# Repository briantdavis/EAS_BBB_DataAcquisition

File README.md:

# EagleAeroSport BeagleBone Black
# Data Acquisition System

This REPO is intended to be extracted into the folder /EAS on the beaglebone black.

Contains code C++ compiled directly on the BBB, using the debian GCC tool chain.

Key files:<br>
PCA9544 - I2C Mux<br>
ADXL345 - I2C 3-axis Accelerometer<br>
BME280  - I2C Pressure, Humidity & Temperature<br>
MPU6050 - I2C 3-axis Accelerometer & 3-axis Gyro<br>
hscPress- AMSYS AMS59xx series pressure sensors<br>

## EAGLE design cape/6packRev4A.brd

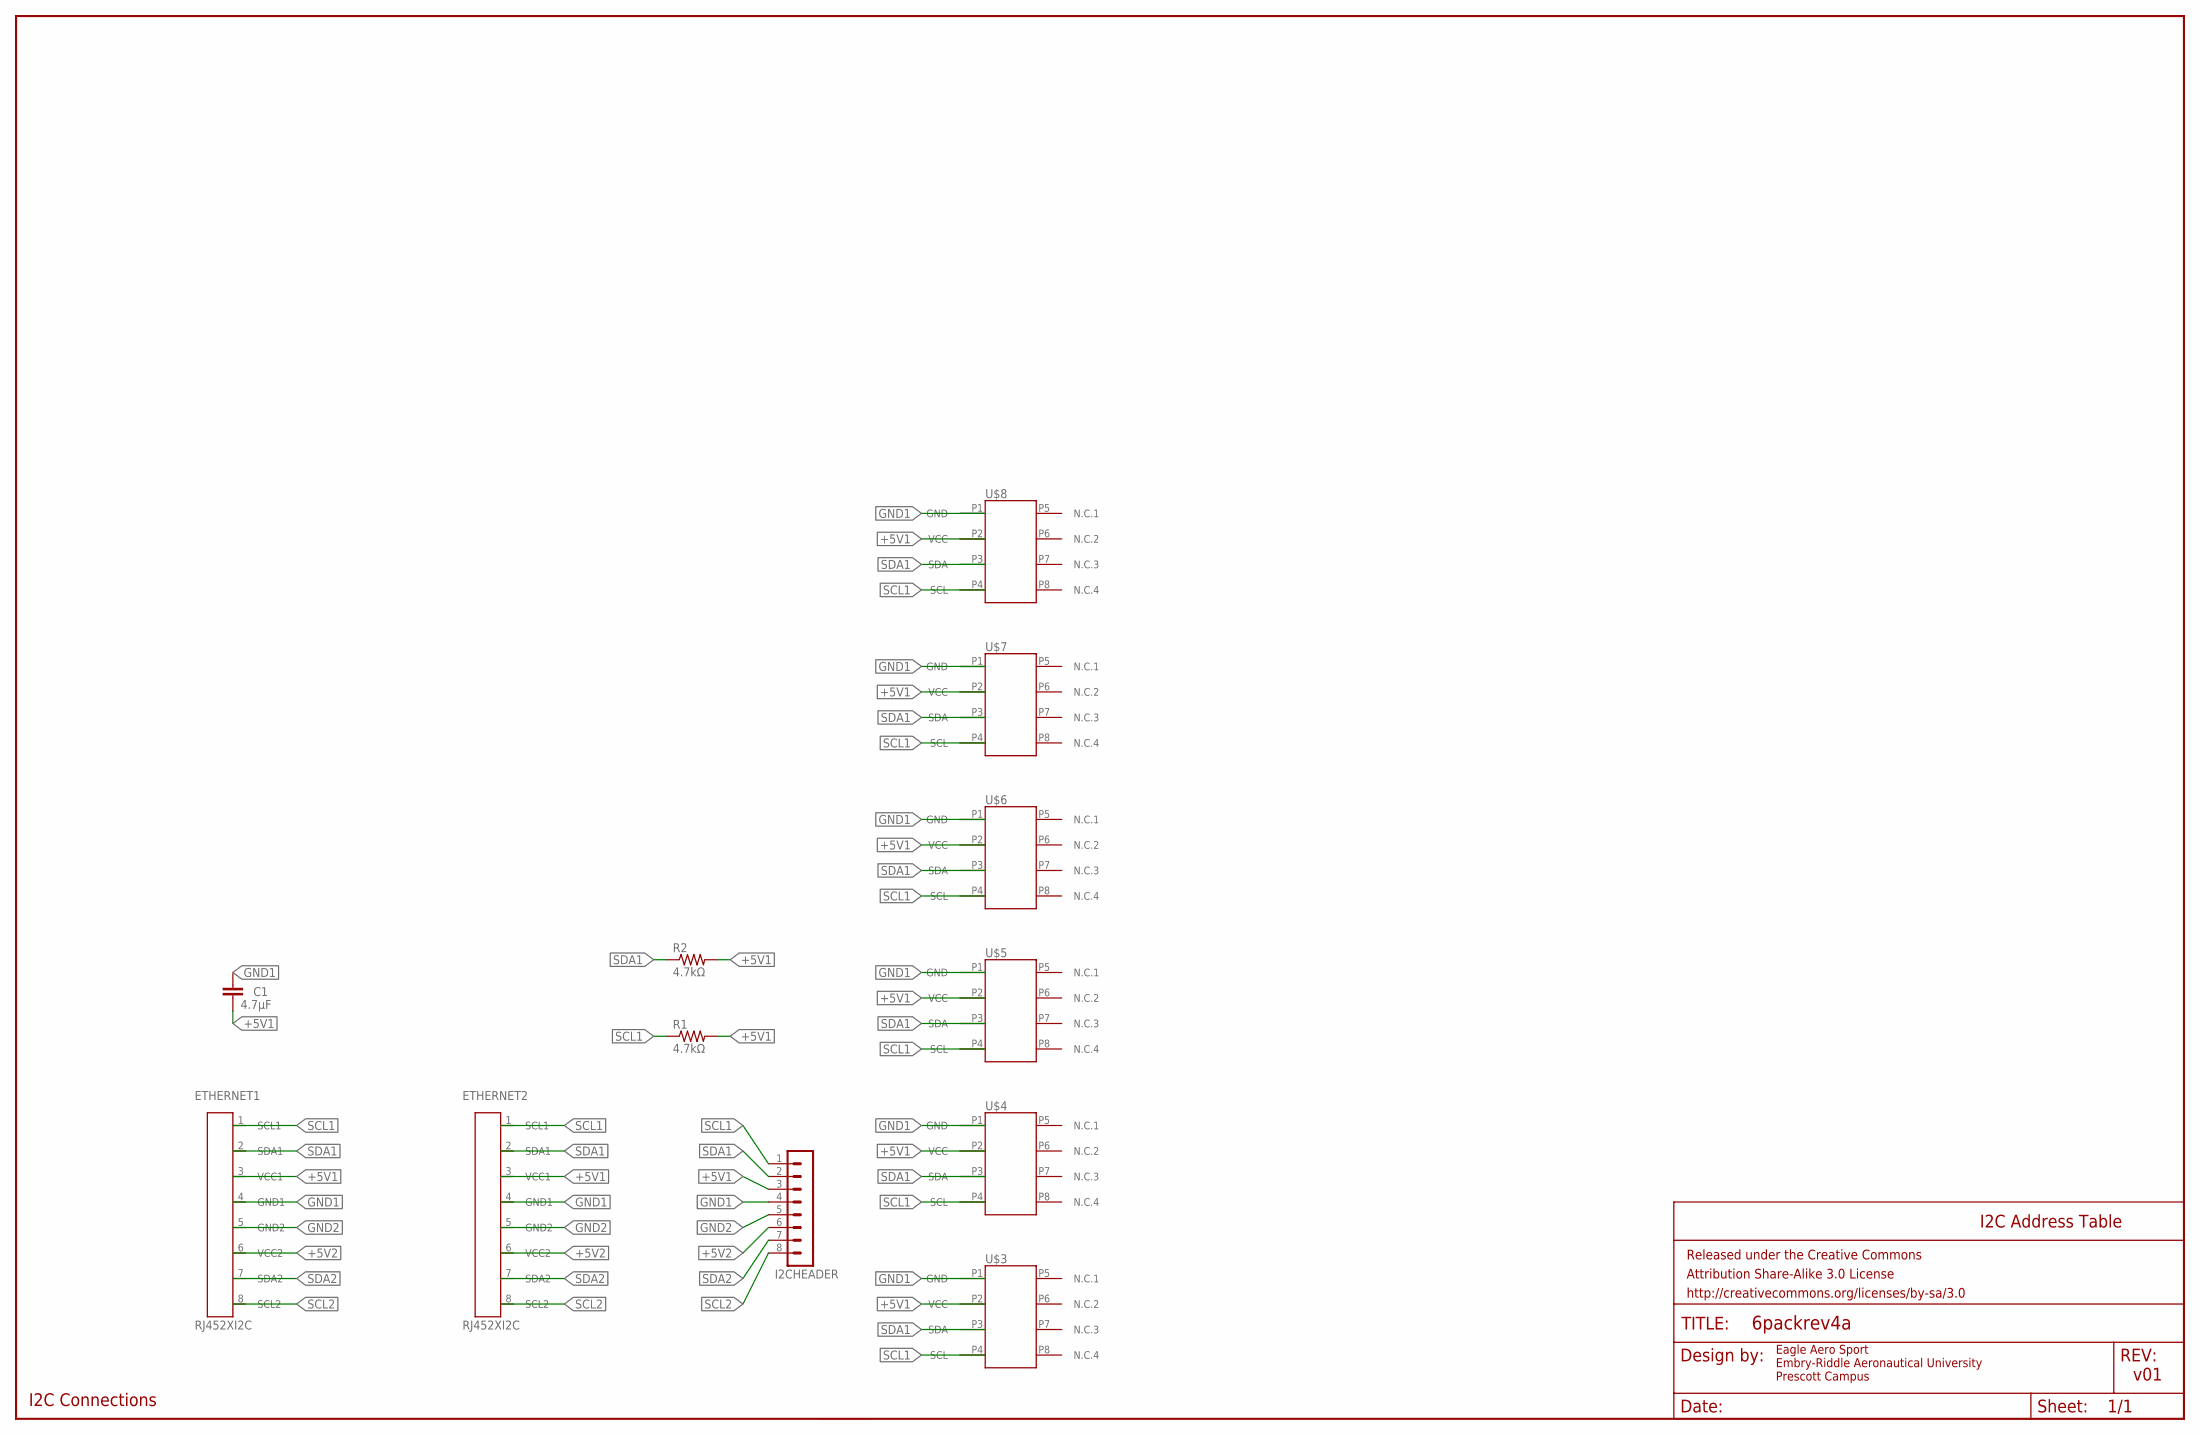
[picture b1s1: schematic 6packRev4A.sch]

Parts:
C1: 4.7µF; CAP-PTH-10MM
ETHERNET1, ETHERNET2: RJ452XI2C; RJ45-8
FRAME1: FRAME-LEDGER; CREATIVE_COMMONS
I2CHEADER: MA08-1
R1, R2: 4.7kΩ; 0207/12
U$3, U$4, U$5, U$6, U$7, U$8: AMS5915; DIP8W

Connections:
+5V1: C1.2, ETHERNET1.3 (VCC1), ETHERNET2.3 (VCC1), I2CHEADER.3, R1.2, R2.2, U$3.P2 (VCC), U$4.P2 (VCC), U$5.P2 (VCC), U$6.P2 (VCC), U$7.P2 (VCC), U$8.P2 (VCC)
+5V2: ETHERNET1.6 (VCC2), ETHERNET2.6 (VCC2), I2CHEADER.6
GND1: C1.1, ETHERNET1.4 (GND1), ETHERNET2.4 (GND1), I2CHEADER.4, U$3.P1 (GND), U$4.P1 (GND), U$5.P1 (GND), U$6.P1 (GND), U$7.P1 (GND), U$8.P1 (GND)
GND2: ETHERNET1.5 (GND2), ETHERNET2.5 (GND2), I2CHEADER.5
SCL1: ETHERNET1.1 (SCL1), ETHERNET2.1 (SCL1), I2CHEADER.1, R1.1, U$3.P4 (SCL), U$4.P4 (SCL), U$5.P4 (SCL), U$6.P4 (SCL), U$7.P4 (SCL), U$8.P4 (SCL)
SCL2: ETHERNET1.8 (SCL2), ETHERNET2.8 (SCL2), I2CHEADER.8
SDA1: ETHERNET1.2 (SDA1), ETHERNET2.2 (SDA1), I2CHEADER.2, R2.1, U$3.P3 (SDA), U$4.P3 (SDA), U$5.P3 (SDA), U$6.P3 (SDA), U$7.P3 (SDA), U$8.P3 (SDA)
SDA2: ETHERNET1.7 (SDA2), ETHERNET2.7 (SDA2), I2CHEADER.7

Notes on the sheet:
I2C Address Table
v01
Eagle Aero Sport Embry-Riddle Aeronautical University Prescott Campus
I2C Connections

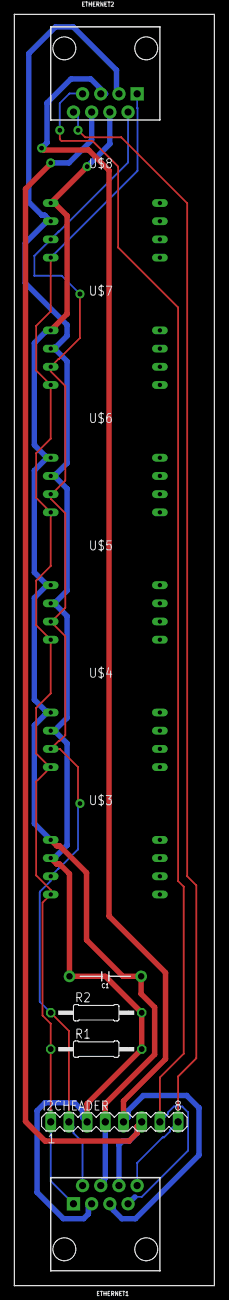
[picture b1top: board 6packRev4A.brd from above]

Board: 2 copper layers, 27.9 x 177.5 mm, 13 parts (0 on the bottom side), 8 nets.

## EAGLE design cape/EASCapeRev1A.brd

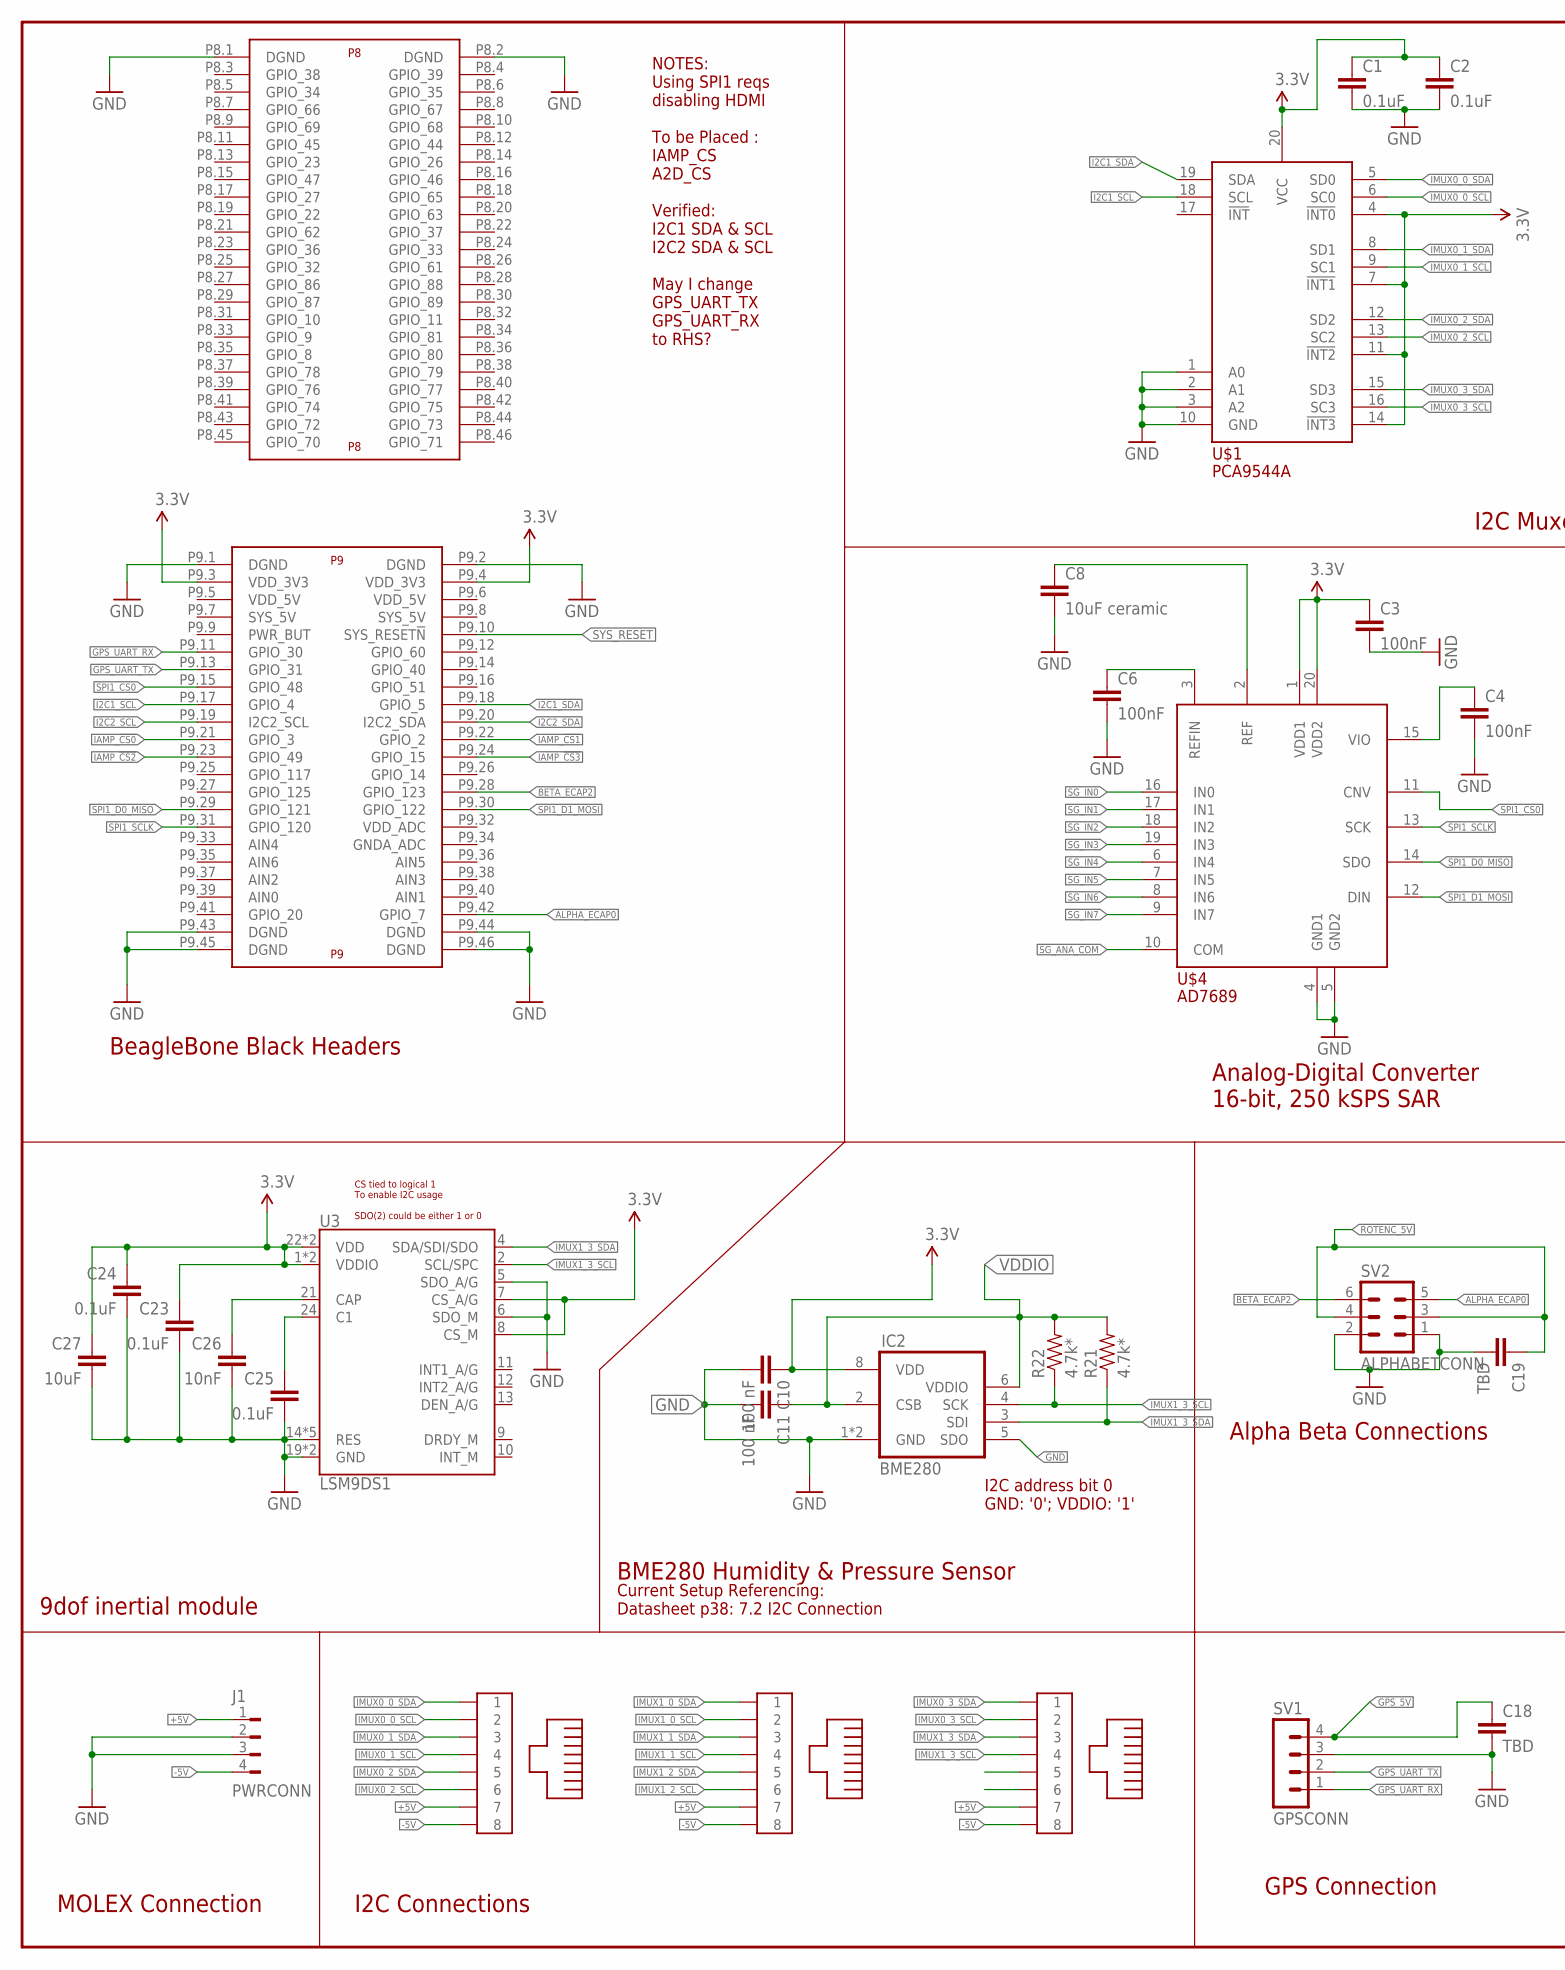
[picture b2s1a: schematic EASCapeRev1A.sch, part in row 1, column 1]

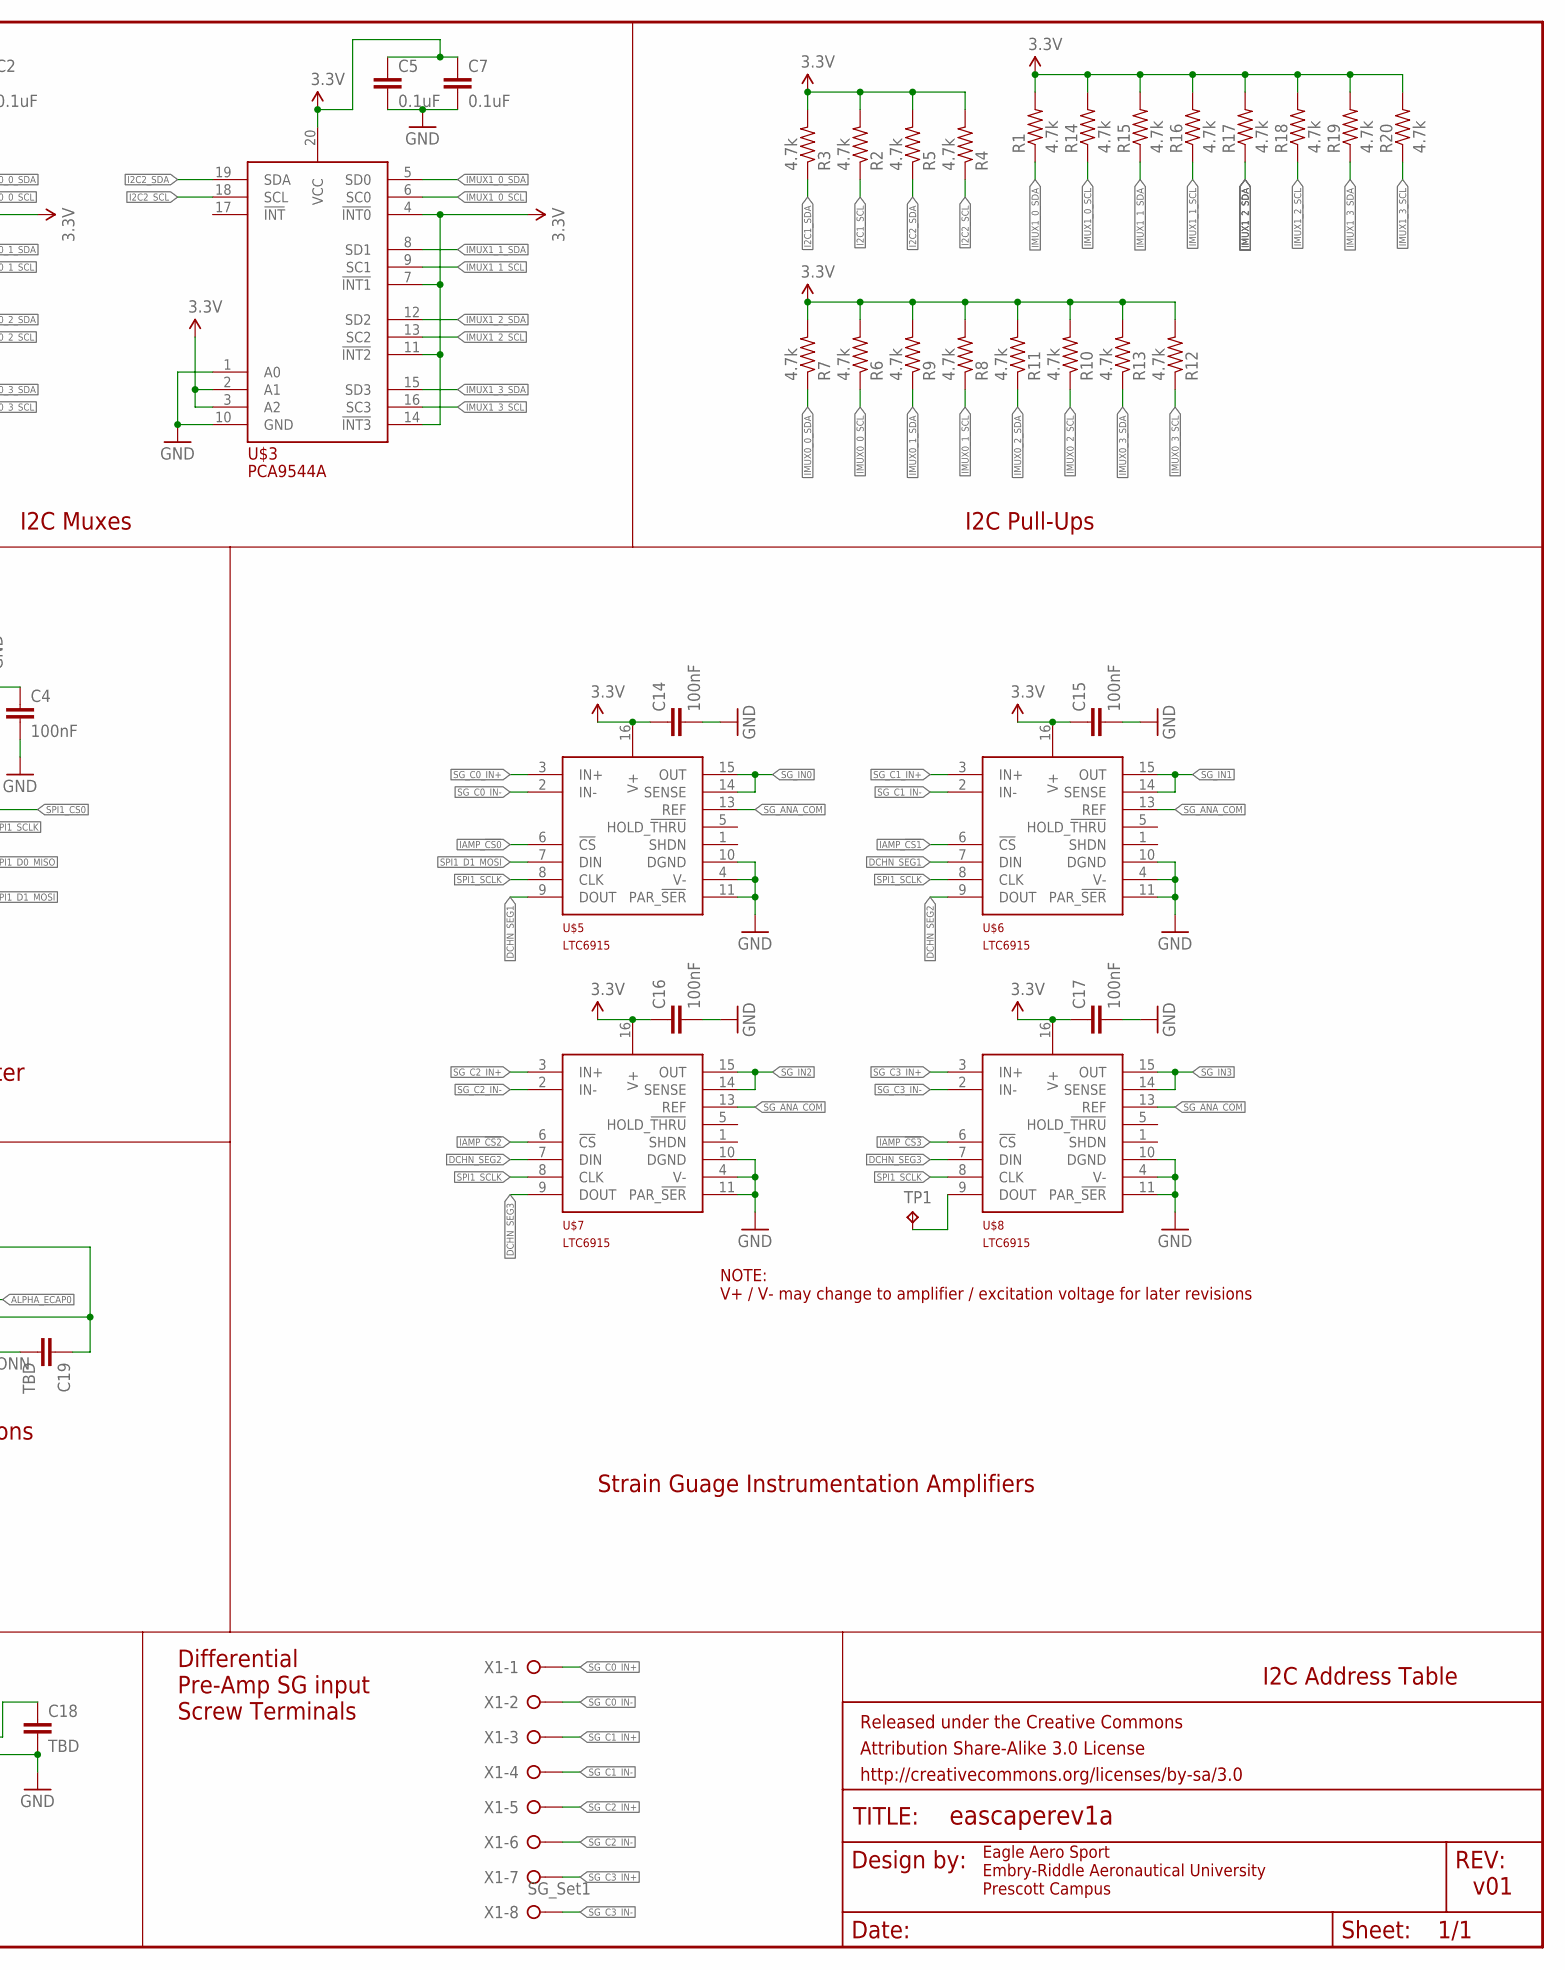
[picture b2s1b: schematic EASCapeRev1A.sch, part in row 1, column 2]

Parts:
C1, C2, C5, C7, C23, C24, C25: 0.1uF; 0805
C3, C4, C6, C14, C15, C16, C17: 100nF; 0805
C8: 10uF ceramic; 0805
C10, C11: 100 nF; 0805
C18, C19: TBD; 0805
C26: 10nF; 0805
C27: 10uF; 0805
FRAME1: FRAME-LEDGER; CREATIVE_COMMONS
IC2: BME280
J1: PWRCONN; 350211
R1, R2, R3, R4, R5, R6, R7, R8, R9, R10, R11, R12, R13, R14, R15, R16, R17, R18, R19, R20: 4.7k; 0805
R21, R22: 4.7k*; 0805
RJ1, RJ2, RJ3: MOLEX-RJ45-SMT
SV1: GPSCONN; MA04-1
SV2: ALPHABETCONN; MA03-2
TP1: TPTP08R; TP08R
U3: LSM9DS1; LGA24-8X4
U$1, U$3: PCA9544A; TSSOP20
U$2: BEAGLE_BONE_BLACK_CAPE
U$4: AD7689; QFN20
U$5, U$6, U$7, U$8: LTC6915; SSOP16
X1: SG_Set1; W237-8P

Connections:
3.3V: C1.1, C2.1, C3.1, C5.1, C7.1, C10.1, C14.1, C15.1, C16.1, C17.1, C23.1, C24.1, C27.1, IC2.8 (VDD), R1.2, R2.2, R3.2, R4.2, R5.2, R6.2, R7.2, R8.2, R9.2, R10.2, R11.2, R12.2, R13.2, R14.2, R15.2, R16.2, R17.2, R18.2, R19.2, R20.2, U3.1 (VDDIO), U3.3 (VDDIO), U3.7 (CS_A/G), U3.8 (CS_M), U3.22 (VDD), U3.23 (VDD), U$1.4 (!INT0!), U$1.7 (!INT1!), U$1.11 (!INT2!), U$1.14 (!INT3!), U$1.20 (VCC), U$2.P9.3 (VDD_3V3), U$2.P9.4 (VDD_3V3), U$3.2 (A1), U$3.3 (A2), U$3.4 (!INT0!), U$3.7 (!INT1!), U$3.11 (!INT2!), U$3.14 (!INT3!), U$3.20 (VCC), U$4.1 (VDD1), U$4.20 (VDD2), U$5.16 (V+), U$6.16 (V+), U$7.16 (V+), U$8.16 (V+)
+5V: J1.1, RJ1.7, RJ2.7, RJ3.7
-5V: J1.4, RJ1.8, RJ2.8, RJ3.8
ALPHA_ECAP0: SV2.5, U$2.P9.42 (GPIO_7)
BETA_ECAP2: SV2.6, U$2.P9.28 (GPIO_123)
C1: C25.1, U3.24 (C1)
CAP: C26.1, U3.21 (CAP)
DCHN_SEG1: U$5.9 (DOUT), U$6.7 (DIN)
DCHN_SEG2: U$6.9 (DOUT), U$7.7 (DIN)
DCHN_SEG3: U$7.9 (DOUT), U$8.7 (DIN)
GND: C1.2, C2.2, C3.2, C4.2, C5.2, C6.2, C7.2, C8.2, C10.2, C11.2, C14.2, C15.2, C16.2, C17.2, C18.2, C19.2, C23.2, C24.2, C25.2, C26.2, C27.2, IC2.1 (GND), IC2.5 (SDO), IC2.7 (GND), J1.2, J1.3, SV1.3, SV2.1, SV2.2, U3.5 (SDO_A/G), U3.6 (SDO_M), U3.14 (RES), U3.15 (RES), U3.16 (RES), U3.17 (RES), U3.18 (RES), U3.19 (GND), U3.20 (GND), U$1.1 (A0), U$1.2 (A1), U$1.3 (A2), U$1.10 (GND), U$2.P8.1 (DGND), U$2.P8.2 (DGND), U$2.P9.1 (DGND), U$2.P9.2 (DGND), U$2.P9.43 (DGND), U$2.P9.44 (DGND), U$2.P9.45 (DGND), U$2.P9.46 (DGND), U$3.1 (A0), U$3.10 (GND), U$4.4 (GND1), U$4.5 (GND2), U$5.4 (V-), U$5.10 (DGND), U$5.11 (PAR_!SER!), U$6.4 (V-), U$6.10 (DGND), U$6.11 (PAR_!SER!), U$7.4 (V-), U$7.10 (DGND), U$7.11 (PAR_!SER!), U$8.4 (V-), U$8.10 (DGND), U$8.11 (PAR_!SER!)
GPS_5V: C18.1, SV1.4
GPS_UART_RX: SV1.1, U$2.P9.11 (GPIO_30)
GPS_UART_TX: SV1.2, U$2.P9.13 (GPIO_31)
I2C1_SCL: R2.1, U$1.18 (SCL), U$2.P9.17 (GPIO_4)
I2C1_SDA: R3.1, U$1.19 (SDA), U$2.P9.18 (GPIO_5)
I2C2_SCL: R4.1, U$2.P9.19 (I2C2_SCL), U$3.18 (SCL)
I2C2_SDA: R5.1, U$2.P9.20 (I2C2_SDA), U$3.19 (SDA)
IAMP_!CS0!: U$2.P9.21 (GPIO_3), U$5.6 (!CS!)
IAMP_!CS1!: U$2.P9.22 (GPIO_2), U$6.6 (!CS!)
IAMP_!CS2!: U$2.P9.23 (GPIO_49), U$7.6 (!CS!)
IAMP_!CS3!: U$2.P9.24 (GPIO_15), U$8.6 (!CS!)
IMUX0_0_SCL: R6.1, RJ1.2, U$1.6 (SC0)
IMUX0_0_SDA: R7.1, RJ1.1, U$1.5 (SD0)
IMUX0_1_SCL: R8.1, RJ1.4, U$1.9 (SC1)
IMUX0_1_SDA: R9.1, RJ1.3, U$1.8 (SD1)
IMUX0_2_SCL: R10.1, RJ1.6, U$1.13 (SC2)
IMUX0_2_SDA: R11.1, RJ1.5, U$1.12 (SD2)
IMUX0_3_SCL: R12.1, RJ3.2, U$1.16 (SC3)
IMUX0_3_SDA: R13.1, RJ3.1, U$1.15 (SD3)
IMUX1_0_SCL: R14.1, RJ2.2, U$3.6 (SC0)
IMUX1_0_SDA: R1.1, RJ2.1, U$3.5 (SD0)
IMUX1_1_SCL: R16.1, RJ2.4, U$3.9 (SC1)
IMUX1_1_SDA: R15.1, RJ2.3, U$3.8 (SD1)
IMUX1_2_SCL: R18.1, RJ2.6, U$3.13 (SC2)
IMUX1_2_SDA: R17.1, RJ2.5, U$3.12 (SD2)
IMUX1_3_SCL: IC2.4 (SCK), R20.1, R22.1, RJ3.4, U3.2 (SCL/SPC), U$3.16 (SC3)
IMUX1_3_SDA: IC2.3 (SDI), R19.1, R21.1, RJ3.3, U3.4 (SDA/SDI/SDO), U$3.15 (SD3)
unnamed: C6.1, U$4.3 (REFIN)
unnamed: C8.1, U$4.2 (REF)
unnamed: C4.1, U$4.15 (VIO)
unnamed: TP1.TP, U$8.9 (DOUT)
ROTENC_5V: C19.1, SV2.3, SV2.4
SG_ANA_COM: U$4.10 (COM), U$5.13 (REF), U$6.13 (REF), U$7.13 (REF), U$8.13 (REF)
SG_C0_IN+: U$5.3 (IN+), X1.1
SG_C0_IN-: U$5.2 (IN-), X1.2
SG_C1_IN+: U$6.3 (IN+), X1.3
SG_C1_IN-: U$6.2 (IN-), X1.4
SG_C2_IN+: U$7.3 (IN+), X1.5
SG_C2_IN-: U$7.2 (IN-), X1.6
SG_C3_IN+: U$8.3 (IN+), X1.7
SG_C3_IN-: U$8.2 (IN-), X1.8
SG_IN0: U$4.16 (IN0), U$5.14 (SENSE), U$5.15 (OUT)
SG_IN1: U$4.17 (IN1), U$6.14 (SENSE), U$6.15 (OUT)
SG_IN2: U$4.18 (IN2), U$7.14 (SENSE), U$7.15 (OUT)
SG_IN3: U$4.19 (IN3), U$8.14 (SENSE), U$8.15 (OUT)
SG_IN4: U$4.6 (IN4)
SG_IN5: U$4.7 (IN5)
SG_IN6: U$4.8 (IN6)
SG_IN7: U$4.9 (IN7)
SPI1_CS0: U$2.P9.15 (GPIO_48), U$4.11 (CNV)
SPI1_D0_MISO: U$2.P9.29 (GPIO_121), U$4.14 (SDO)
SPI1_D1_MOSI: U$2.P9.30 (GPIO_122), U$4.12 (DIN), U$5.7 (DIN)
SPI1_SCLK: U$2.P9.31 (GPIO_120), U$4.13 (SCK), U$5.8 (CLK), U$6.8 (CLK), U$7.8 (CLK), U$8.8 (CLK)
SYS_RESET: U$2.P9.10 (SYS_RESET!N)
VDDIO: C11.1, IC2.2 (CSB), IC2.6 (VDDIO), R21.2, R22.2

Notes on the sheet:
BeagleBone Black Headers
I2C Address Table
v01
Eagle Aero Sport Embry-Riddle Aeronautical University Prescott Campus
I2C Muxes
Analog-Digital Converter 16-bit, 250 kSPS SAR
CS tied to logical 1 To enable I2C usage SDO(2) could be either 1 or 0
9dof inertial module
Strain Guage Instrumentation Amplifiers
Differential Pre-Amp SG input Screw Terminals
I2C Pull-Ups
I2C Connections
NOTES: Using SPI1 reqs disabling HDMI To be Placed : IAMP_CS A2D_CS Verified: I2C1 SDA & SCL I2C2 SDA & SCL May I change GPS_UART_TX GPS_UART_RX to RHS?
NOTE: V+ / V- may change to amplifier / excitation voltage for later revisions
GPS Connection
Alpha Beta Connections
MOLEX Connection
BME280 Humidity & Pressure Sensor
Current Setup Referencing: Datasheet p38: 7.2 I2C Connection
I2C address bit 0 GND: '0'; VDDIO: '1'

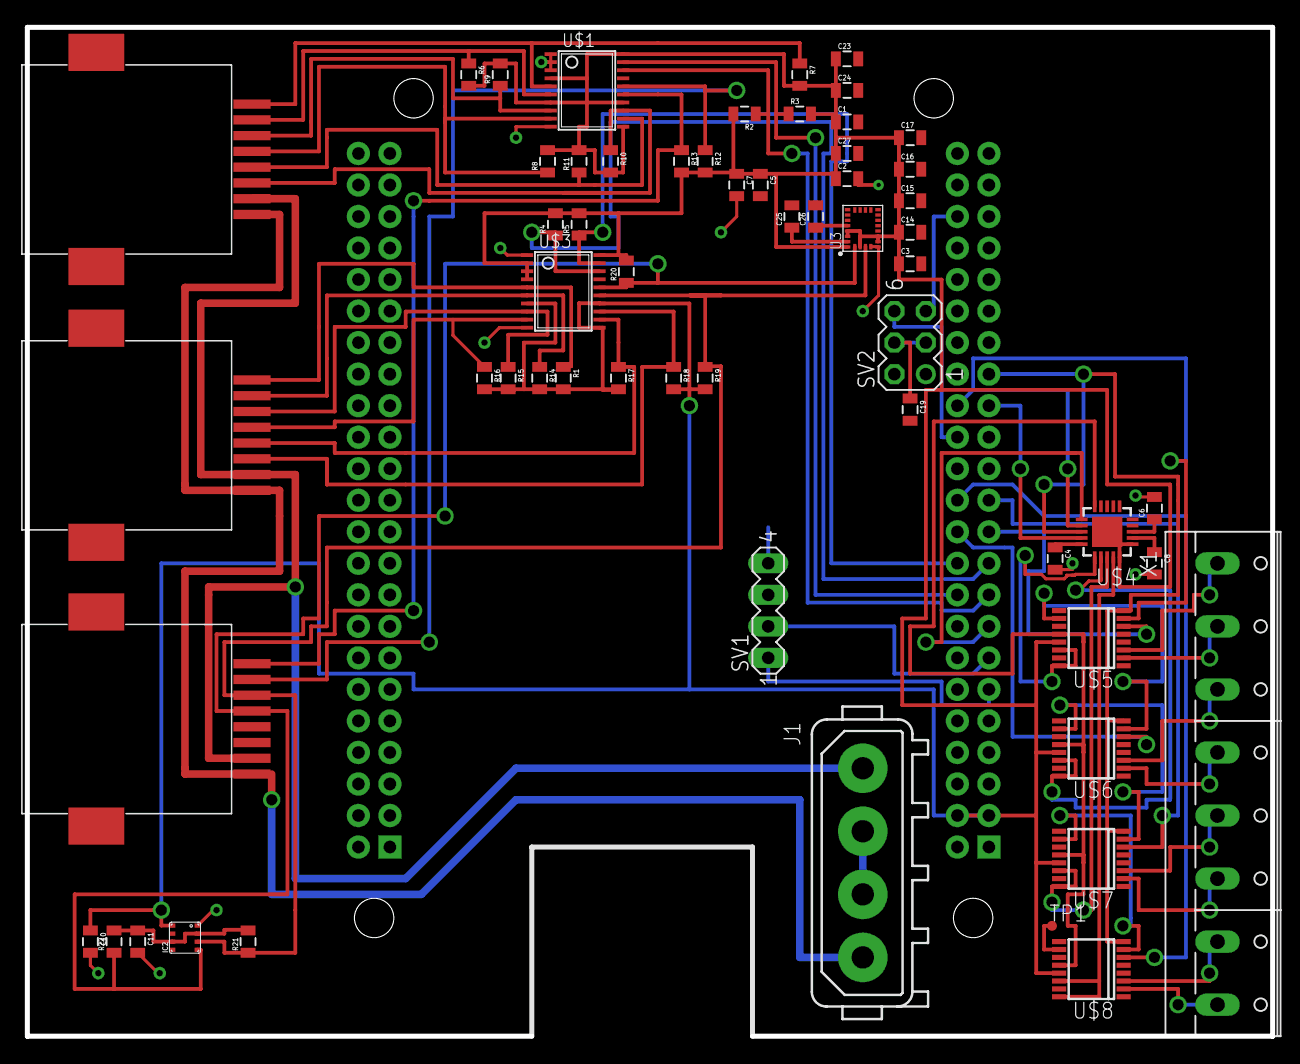
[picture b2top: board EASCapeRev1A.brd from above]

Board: 2 copper layers, 100.3 x 81.3 mm, 62 parts (1 on the bottom side), 61 nets.

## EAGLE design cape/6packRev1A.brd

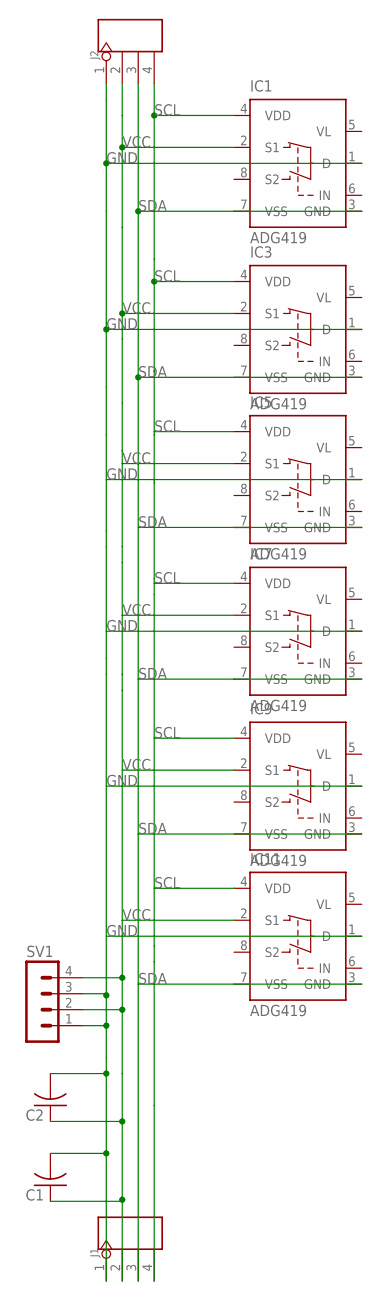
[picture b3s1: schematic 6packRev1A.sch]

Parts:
C1, C2: C-USC0805; C0805
IC1, IC3, IC5, IC7, IC9, IC11: ADG419; DIL08
J1, J2: HEADER-4P-80/40MIL; 4P-2.54-80/40MIL
SV1: MA04-1

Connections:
GND: C1.2, C2.2, IC1.1 (D), IC3.1 (D), IC5.1 (D), IC7.1 (D), IC9.1 (D), IC11.1 (D), J1.1, J2.1, SV1.1, SV1.3
SCL: IC1.4 (VDD), IC3.4 (VDD), IC5.4 (VDD), IC7.4 (VDD), IC9.4 (VDD), IC11.4 (VDD), J1.4, J2.4
SDA: IC1.3 (GND), IC1.7 (VSS), IC3.3 (GND), IC3.7 (VSS), IC5.3 (GND), IC5.7 (VSS), IC7.3 (GND), IC7.7 (VSS), IC9.3 (GND), IC11.3 (GND), J1.3, J2.3
VCC: C1.1, C2.1, IC1.2 (S1), IC3.2 (S1), IC5.2 (S1), IC7.2 (S1), IC9.2 (S1), IC11.2 (S1), J1.2, J2.2, SV1.2, SV1.4
VL: IC1.5 (VL), IC3.5 (VL), IC5.5 (VL), IC7.5 (VL), IC9.5 (VL), IC11.5 (VL)
VSS: IC9.7 (VSS), IC11.7 (VSS)

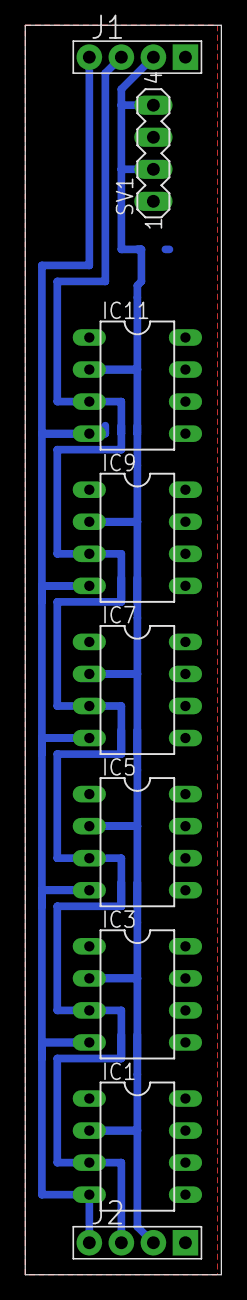
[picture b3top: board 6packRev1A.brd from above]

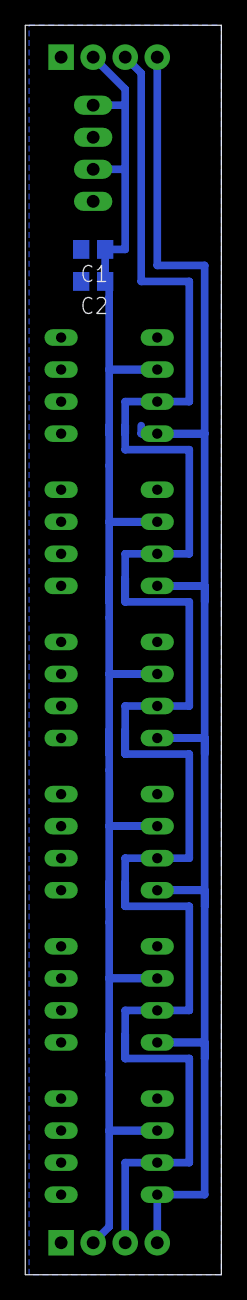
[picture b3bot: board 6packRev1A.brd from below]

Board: 2 copper layers, 15.5 x 99.0 mm, 11 parts (2 on the bottom side), 6 nets.

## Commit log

2015-10-27 Repository creation
2015-10-27 To avoid blank pull
2015-10-27 Added directory for TinyConsole
2015-11-11 bmp180 baroSen(I2C_HW1_BUS_NUM);
2015-11-11 Updated for faster operation & somewhat array oriented
2015-11-11 Add support for Honeywell HSC Sensors
2015-11-11 Update DAQ pack for HSC additions
2015-11-12 Init script updated to work with the new EAS file structure.
    Time to boot reduced from 4-5 minutes to 10-15 seconds
    gh-6
2015-11-12 added startup files and a short description and how-to to the git project folder. Needs testing.
2015-11-12 Can you say Nanoseconds?!?!?!
    Hopefully this is a helpful commit.
    The folder "Time" contains a c++ file that might help our time issue.
    Please read the comments of "time.cpp" to understand how to compile it.
    If more comments are needed, simply notify me.
2015-11-12 EASClient ntp config
2015-11-12 This is an indev init file for the RV12.
    DO NOT RUN BEFORE PERFORMING A BACKUP -- stability unconfirmed
    Reason for commit: backup
    Current purpose of files:
    EAS-RV12-Startup can be added to the boot script WITHOUT editing the uEnv.txt by:
    1). Copying the Script and associated files into "/etc/init.d" which places the file into the initialization folder
    2). Running the command "chmod +x /etc/init.d/EAS-RV12-Startup" which gives the file executeable status
2015-11-12 testing pulls.
2015-11-19 Added Support for BME280 Pressure, Temperature, Humidity Sensor
2015-11-19 Changes to Source to support BME280 and fix /log missing hang, etc..
2015-11-20 Updated Makefile - removed specific rule, changed executable
2016-02-04 Delete Time Executable
    Executables should not be included in Commits, they can be created from Source.
2016-02-05 gh-006
    I updated the init script to locate and execute any one file.
    The folder "testenv" may soon be deleted.
    Currently, the script will locate and execute "Enable_third_i2c.sh"
    WARNING: THIS CODE MAY NEED ERROR MANAGEMENT
    The code will also dump all console output into logs during the execution of it.
    As well as any logs you would typically see from the other scripts.
2016-02-05 File Clean-up
2016-02-05 Revert "File Clean-up"
    This reverts commit 4fbeb352dc03b891872d8e0116ea5f7071236f97.
2016-02-05 Revert "gh-006"
    This reverts commit bcb2b0c533f54fa78715ce4390292b0445f2dfd3.
2016-02-05 gh-6 I updated the init script to locate and execute any one file. The folder "testenv" may soon be deleted.
    Currently, the script will locate and execute "Enable_third_i2c.sh"
    WARNING: THIS CODE MAY NEED ERROR MANAGEMENT
    The code will also dump all console output into logs during the execution of it.
    As well as any logs you would typically see from the other scripts.
    These logs can be found in:
    "/logs/[filename].log"
2016-02-06 Working Init Script gh-6
    I have officially gotten the init script to work.
    Apparently, my issue, as we discussed, was as simple as a bad directory call.
    This code executes a led sweep sequence on start-up ("EAS-RV12-Startup-Leds.sh") and then executes "Enable_third_i2c.sh"
    When shutting down, this code will flash all leds simultaneously for a while ("EAS-RV12-Shutdown-Leds.sh")
    The Led flashes are only used as debug code and are not inherently necessary.
    However, something you may be interested in knowing:
2016-02-06 Deleted 'testenv' and its contents as well as a needless "README.txt".
2016-02-08 Update EAS-RV12-Startup.sh
    minor variable fix
2016-02-08 Grammar Fixes
    Grammar Fixes
2016-02-09 Changed directory structure; First commit from BBB
2016-02-09 Added logs directory, or RM within; Second commit from BBB
2016-02-09 Added bin directory
2016-02-09 Updated makefile for new /bin directory
2016-02-09 Update .gitignore
    Add .log to avoid committing to repo
2016-02-09 removed logs from source
2016-02-09 Update README.md
    Editted to reflect the /EAS intended destination of the Repo
2016-02-09 new branch, working on timestamps
2016-02-09 Update eas_daq_pack.h
    Added a datatype for the easDAQpackData_t to allow pointers to the union within a daq pack as desired for the Decoder.
2016-02-10 dual timestamp operational
2016-02-11 Some fixes to the Startup to support the new file structure.
    Test code comparisons for mono and real added.
    gh-13 gh-12
2016-02-16 new versions of sch/brd in /cape; added /docs
2016-02-28 DHCP Server configs for the Intel NUC
2016-02-28 Revert "DHCP Server configs for the Intel NUC"
    This reverts commit aa527788f2af027c317a5f98b5c84bef995809d2.
    Reversion to correct author email
2016-02-28 DHCP Server configd for the Intel NUC
2016-02-28 Update to the config files for DHCP
    WARNING: when applied, these configs effectively disable it's client abilities.
    NOTE: Extra steps will be necessary to return to client conditions
2016-02-29 recover after forced push
2016-02-29 Delete Cape_Block_Diagram.v6.pdf
    Moved to /docs
2016-02-29 Delete EAS.EE.Part_Num_List.vbd2.xlsx
    Moved to /docs
2016-02-29 Delete Sat_Cape.v7.brd
    Old Version
2016-02-29 Delete Sat_Cape.v7.sch
    Old version
2016-03-01 added unique identifer to DAQ_PACK
2016-03-02 added logfile Part A Sensor ID info
2016-03-03 Adding LSM9DS1 headers from Sparkfun Repo
2016-03-03 Updated hscPress to incude PartA logfile data
2016-03-04 Added unique ID to daq pack generated by HSC
2016-03-11 ntp configs
2016-03-14 Added Analog Cape v9 from BBB
2016-03-23 Create SLM9DS1IMU
    LSM9DS1 IMU .h file INCOMPLETE
2016-03-23 Update and rename SLM9DS1IMU to LSM9DS1IMU
2016-03-25 Rename LSM9DS1IMU to LSM9DS1IMU.h
2016-03-25 Create LSM9DS1_Types.h
    Used by LSM9DS1IMU.h
2016-03-25 Create LSM9DS1_Registers.h
    Used by LSM9DS1_Registers.h
2016-05-13 Updated Header References for Rasp3
2016-05-13 makefile for 2 targets
2016-05-13 dual output makefile
2016-09-23 From Office code
2016-09-23 Update README.md
    Deal with Unix/DOS file format inconsistencies
2016-10-18 Pushing the old GPS code
2016-10-18 working NMEA string Parser that needs NMEA definitions to be completed.
2016-10-28 first add_cal commit?
2016-10-28 Cal for BME280 completed ASCII output
2017-09-25 Updated GPS Data Acquisition Code - Functional
    I've revisited the code and modified it to be more readable and now work.
    You can expect me to meet with you, Dr. Davis, this week.
2017-09-25 Delete gpsCOMM.cpp
    This file has been cut up into several pieces to increase readability.
2017-10-23 Update readme.md to mention proper sensor type.
2018-01-22 moved files around, added ntp conf, removed startup folder (redundancy fix)
2018-01-22 Moved client ntp.conf to appropriate folder.
2018-09-28 Initial six pack design
    Rev 1A for the EAS six pack design.
2018-09-28 Cape Complete redesign
    Matt's Complete redesign for the cape
2018-09-28 Cape Fixes
    Update outline for the cape around the ethernet port cutout so that it will be cut out. Move the top of the cape, creating more space for the rj45 jacks.
2018-10-01 Breate rev 1B for six pack
    Create new revision of six pack fixing spacing and pinout issues.
2018-10-01 Make test cape more compact
2018-10-01 Cape 1B try 2
2018-10-09 6 pack version 1C
2018-10-17 Update cape/EASEagle.lbr
    Add custom eagle pats library to github.
2018-10-18 Update BME280 cal_data output
    Now outputs cal_data string to display the calibration string in the same format as the other parts of the header
2018-10-18 Add a space
    I forgot to add a space to the previous commit. It has been added now.
2018-10-22 6Pack 1D
2018-10-24 6Pack version 2A
2018-10-26 Update 6Pack 2A
2018-10-26 Revert "Update 6Pack 2A"
    This reverts commit 827b5304b12bda17fe1987ea76be93996f945791.
2018-10-26 Crete 6Pack Rev 3A
    Fixes issue in rev 2A where resistors were pulling down instead of pulling up.
2018-10-26 Fix footprint cape 3A
2019-02-06 6-pack 4a
    Final production test for 6-pack
2019-02-06 Update cape/6packRev4A.brd
    Fix minor issue with a via position and remove excess text.
2019-02-11 Update .gitignore
    Add some eagle autogenerated files to gitignore.
2019-02-11 Update EASEagle.lbr
    Added two new symbols. RJ454Xsig is the name of the pinout for the analog cape that carries signals to the adc. RJ45I2C2XPWM is a temporary placeholder for the connection that is being used for the p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
    Created a new Device called RJ454XSIG which connects the symbol of the same name to the footprint RJ45-8.
2019-02-11 Update .gitignore
    Add more autogen files to gitignore
2019-03-25 Add base pan flute code for pressure taps.
2019-03-25 Add needed methods to hscPress and outline to pan_flute
2019-03-27 Update pan_flute.cpp
    Add Some more logic to the pan flute code.
2019-09-22 Commit ferrin's old stuff

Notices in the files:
parts and their libraries:
SparkFun-Capacitors: Licensing: Creative Commons ShareAlike 4.0 International - https://creativecommons.org/licenses/by-sa/4.0
SparkFun-Aesthetics: Licensing: CC v3.0 Share-Alike You are welcome to use this library for commercial purposes.
SparkFun-Aesthetics: Released under the Creative Commons
